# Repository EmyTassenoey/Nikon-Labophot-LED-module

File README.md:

# Nikon-Labophot-LED-module
LED module for Nikon Labophot (UV and Visible spectrum)

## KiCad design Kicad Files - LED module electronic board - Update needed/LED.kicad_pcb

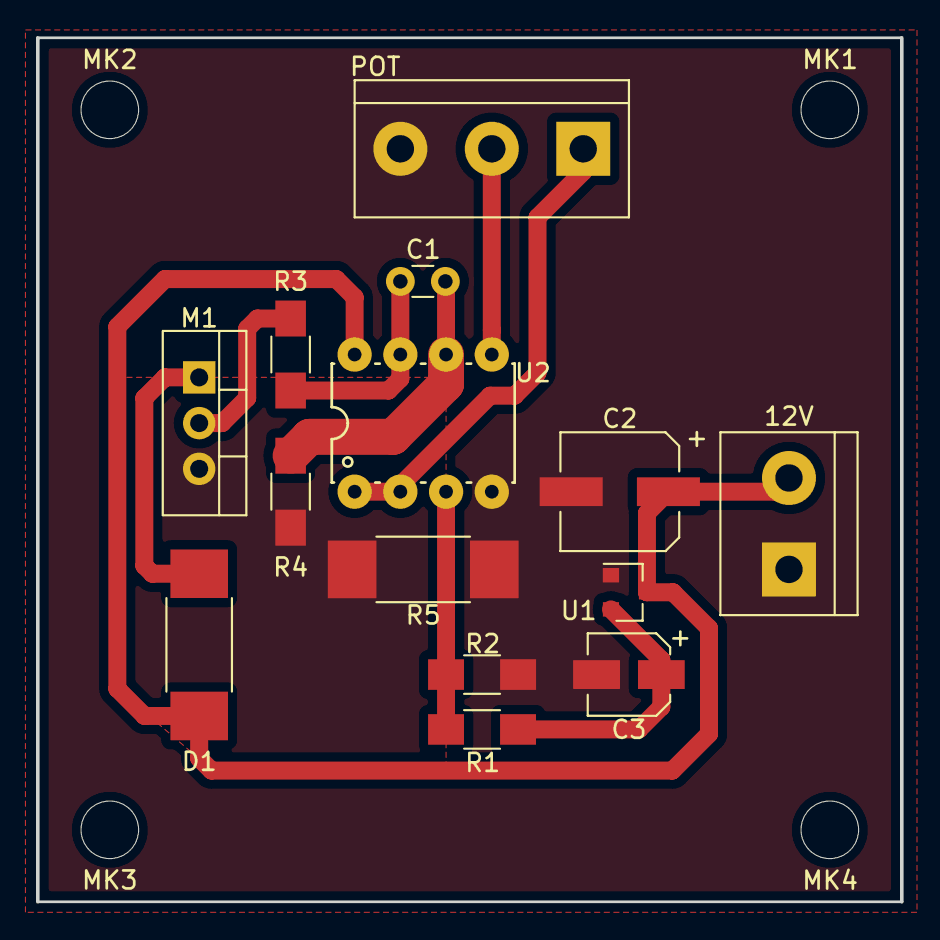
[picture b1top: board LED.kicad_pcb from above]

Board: 2 copper layers, 48.0 x 48.0 mm, 18 parts (0 on the bottom side), 11 nets.

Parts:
12V: Screw_Terminal_01x02; TerminalBlock_bornier-2_P5.08mm
C1: 100nF; C_Disc_D3.0mm_W1.6mm_P2.50mm
C2: 220uF; CP_Elec_6.3x5.3
C3: 10uF; CP_Elec_4x5.3
D1: Cree XHP70 5.8V; R_2512_HandSoldering
M1: P16NF06L; TO-220-3_Vertical
MK1, MK2, MK3, MK4: Mounting_Hole; MountingHole_3.2mm_M3
POT: 1k; TerminalBlock_bornier-3_P5.08mm
R1: 22K; R_1206_HandSoldering
R2: 1K; R_1206_HandSoldering
R3: 220; R_1206_HandSoldering
R4: 10K; R_1206_HandSoldering
R5: 0.05; R_2512_HandSoldering
U1: AMS1117-1.5; SOT-23
U2: LM358; PDIP-8

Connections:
+12V: 12V.2, C2.1, D1.2, U1.3, U2.8
GND: 12V.1, C2.2, C3.2, POT.3, R2.2, R5.2, U1.1, U2.4
unnamed: C1.1, R3.2, U2.7
unnamed: C1.2, R4.2, U2.6
unnamed: C3.1, R1.2, U1.2
unnamed: D1.1, M1.1
unnamed: M1.2, R3.1
unnamed: M1.3, R4.1, R5.1
unnamed: POT.1, U2.1, U2.2
unnamed: POT.2, U2.5
unnamed: R1.1, R2.1, U2.3

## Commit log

2019-03-03 Assembly pictures
2019-03-03 Versions updated
2019-03-19 Major changes!
    Major changes! Do not use older version, pins swapped in V-regulator.
2019-03-19 Minor changes in footprints
